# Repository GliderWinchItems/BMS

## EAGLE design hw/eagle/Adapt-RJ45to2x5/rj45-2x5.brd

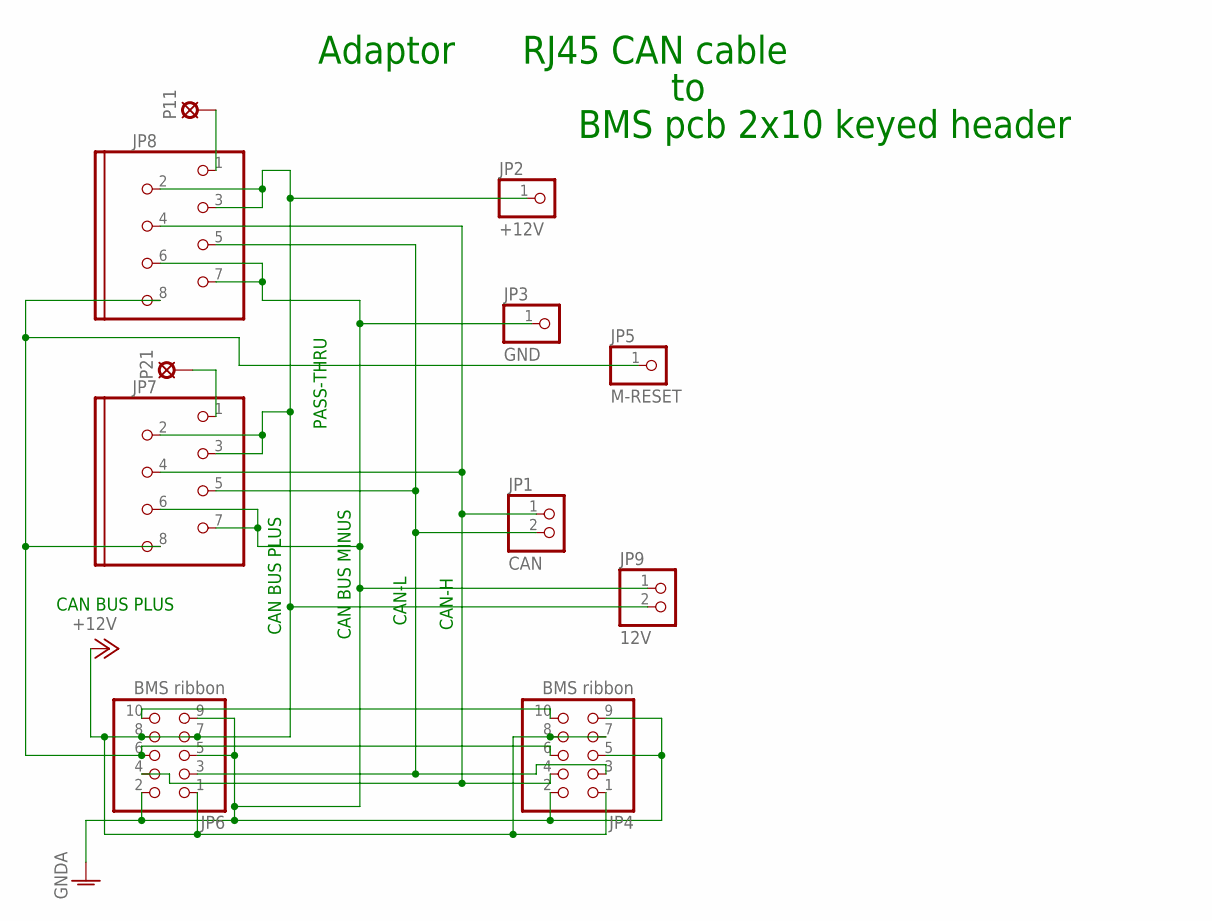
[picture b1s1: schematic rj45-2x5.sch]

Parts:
JP1: CAN; 1X02
JP2: +12V; 1X01
JP3: GND; 1X01
JP4, JP6: BMS ribbon; 2X05_KEYED
JP5: M-RESET; 1X01
JP7, JP8: MOD8P8C
JP9: 12V; 1X02
P11, P21: SOLPAD035; SOLDPAD035

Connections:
+12V: JP2.1, JP4.1, JP4.7, JP4.8, JP6.1, JP6.7, JP6.8, JP7.2 (5), JP7.3 (2), JP8.2 (5), JP8.3 (2), JP9.2
CANCABLE_1_1: JP8.1, P11.MP
CANCABLE_2_1: JP7.1, P21.MP
CANH: JP1.1, JP4.4, JP6.4, JP7.4 (6), JP8.4 (6)
CANL: JP1.2, JP4.3, JP6.3, JP7.5 (3), JP8.5 (3)
GNDA: JP3.1, JP4.2, JP4.5, JP4.9, JP6.2, JP6.5, JP6.9, JP7.6 (7), JP7.7 (4), JP8.6 (7), JP8.7 (4), JP9.1
MASTER-RESET-SYS: JP4.6, JP5.1, JP6.6, JP7.8, JP8.8
unnamed: JP4.10, JP6.10

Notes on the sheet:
CAN BUS PLUS
PASS-THRU
CAN BUS MINUS
CAN-H
CAN-L
Adaptor
RJ45 CAN cable
BMS pcb 2x10 keyed header

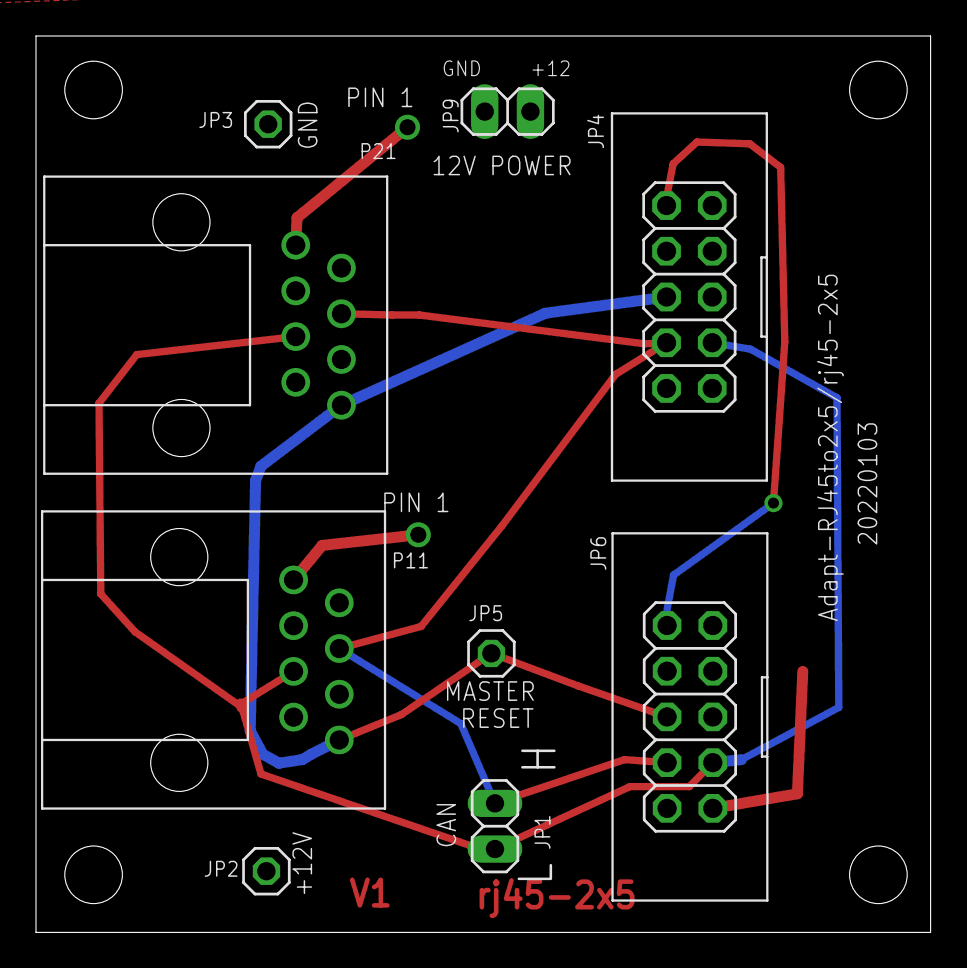
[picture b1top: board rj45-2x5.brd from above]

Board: 2 copper layers, 49.7 x 49.8 mm, 11 parts (0 on the bottom side), 8 nets.
